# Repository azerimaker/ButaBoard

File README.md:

# ButaBoard
This repo contains all the necessary design, fabrication files and example codes for the ButaBoard development board. ButaBoard is highly inspired by the [Adafruit Circuit Playground Classic](https://www.adafruit.com/product/3000) with some minor hardware changes. Additionaly, the paisley patterned styling and ornamental touches make this board more suitable for wearables. 

## Specs:
- ATmega32u4 MCU, running @3.3V, 8MHz
- 32KB Flash, 2.5 KB SRAM, 1KB EEPROM
- IO pins: 14 (Crocodile clip-4mm Banana pads)
- On-board peripherals:
  - LIS3DH Accelerometer 
  - ALS-PT19-315C analog light sensor
  - AOS3729A analog microphone
  - NTC Temperature Sensor
  - Buzzer
  - 12x WS2812B RGB LEDs
  - 1x user button, 1x user LED
  - Power Switch
- Dimenions: ~94x61x5 mm

### ButaBoard v1

<div align="center">
<br />This work is licensed under a <a rel="license" href="http://creativecommons.org/licenses/by-nc-sa/4.0/">Creative Commons Attribution-NonCommercial-ShareAlike 4.0 International License</a>.
</div>

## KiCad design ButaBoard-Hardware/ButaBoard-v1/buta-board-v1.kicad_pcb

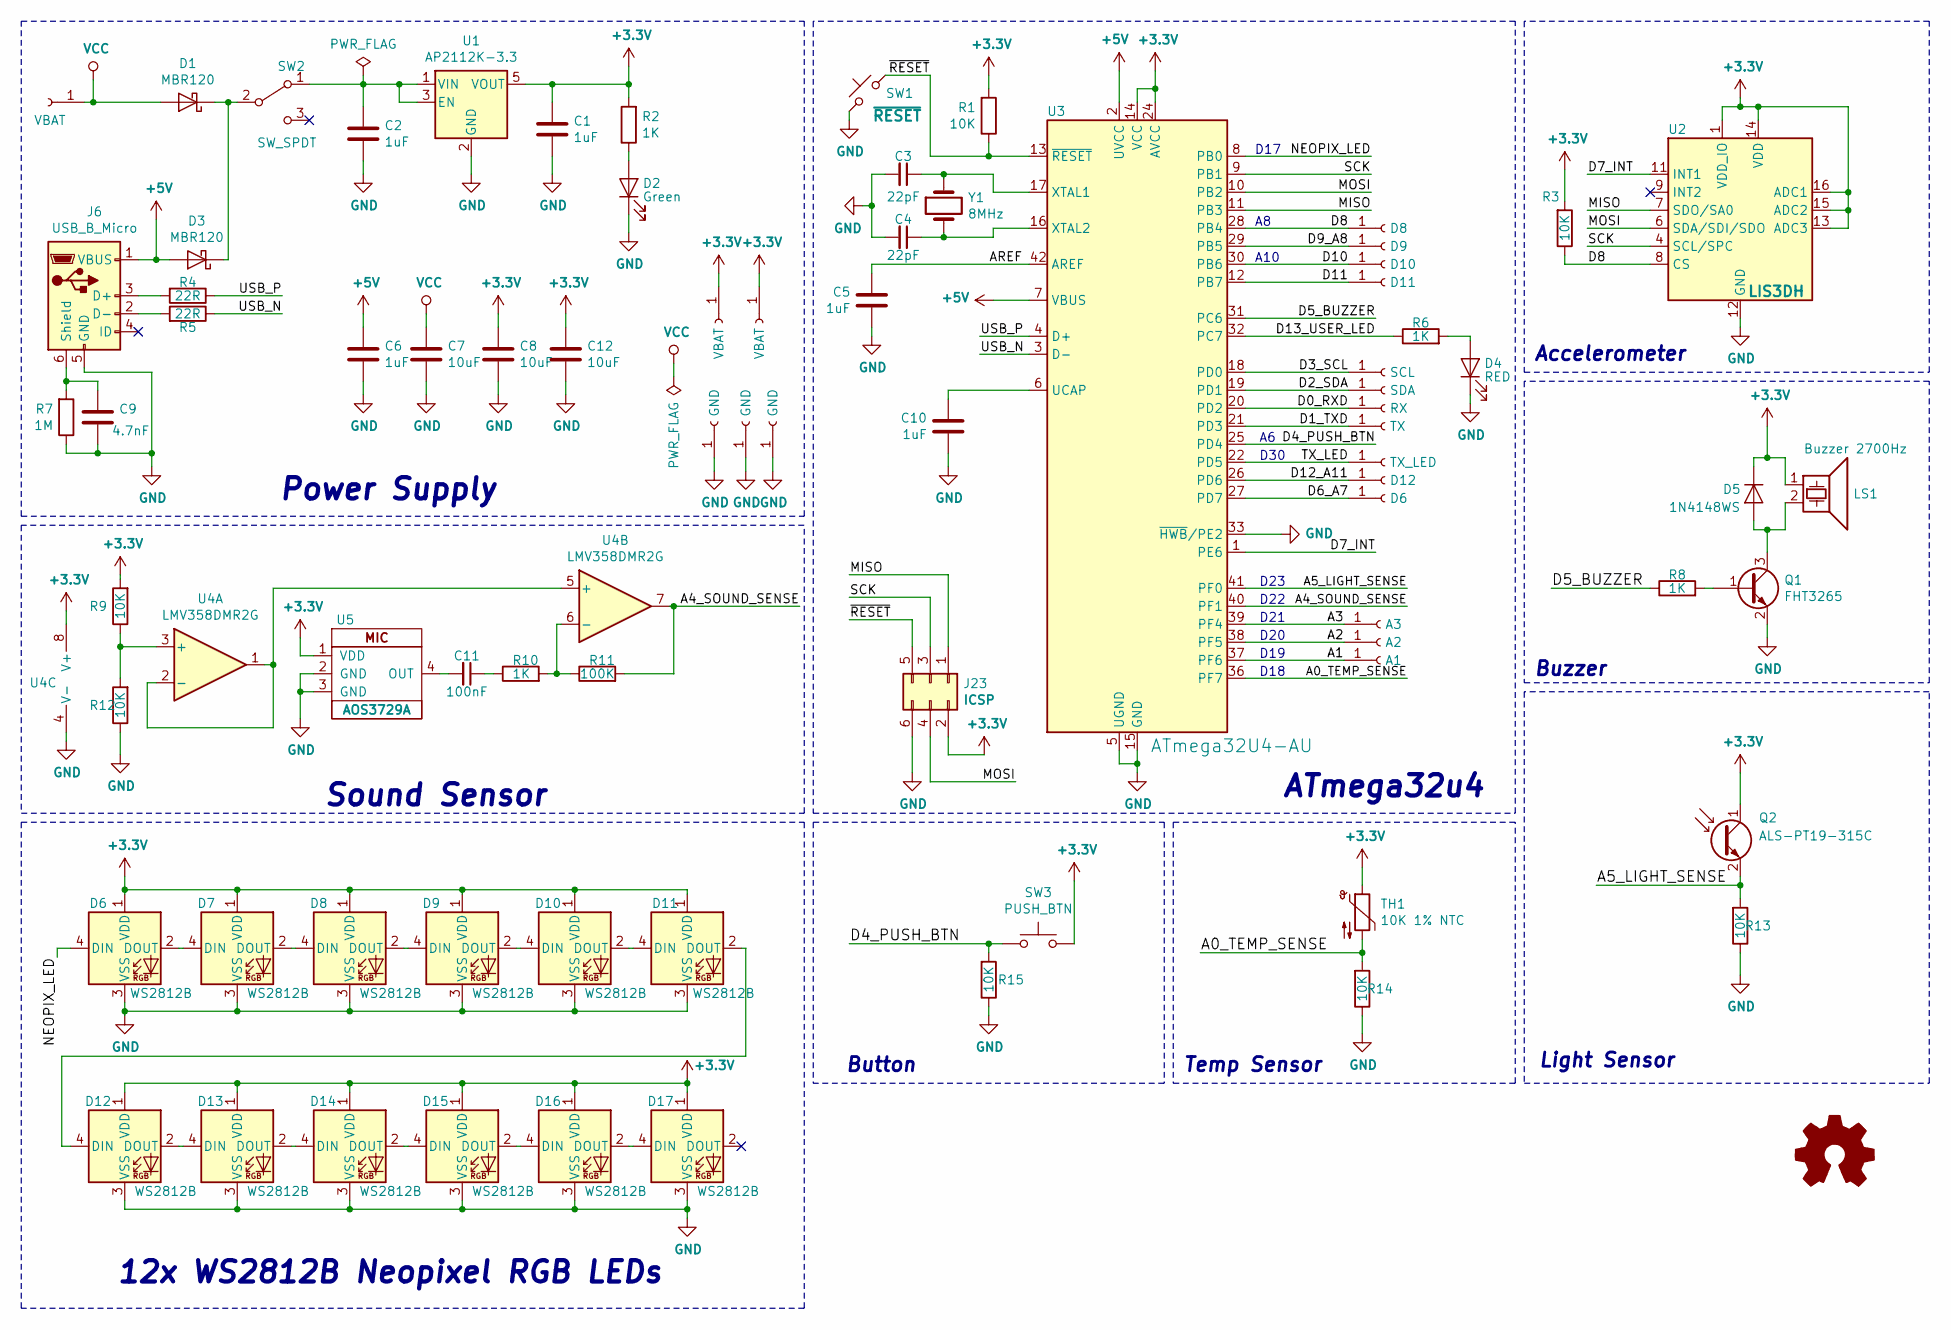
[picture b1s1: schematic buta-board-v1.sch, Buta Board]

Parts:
C1, C2, C5, C6, C10: 1uF; C_0805_2012Metric
C3, C4: 22pF; C_0402_1005Metric
C7, C8, C12: 10uF; C_0805_2012Metric
C9: 4.7nF; C_0805_2012Metric
C11: 100nF; C_0805_2012Metric
D1, D3: MBR120; D_SOD-123; MPN MBR120VLSFT1G
D2: Green; LED_0805_2012Metric
D4: RED; LED_0805_2012Metric
D5: 1N4148WS; D_SOD-323; MPN 1N4148WS
D6, D7, D8, D9, D10, D11, D12, D13, D14, D15, D16, D17: WS2812B; LED_WS2812B_PLCC4_5.0x5.0mm_P3.2mm; MPN WS2812B-B
J2: D8; Alligator_Pads
J3: D9; Alligator_Pads
J4: D10; Alligator_Pads
J5: D11; Alligator_Pads
J6: USB_B_Micro; USB_Micro-B_C10418; MPN C10418
J7, J8, J9: GND; Alligator_Pads
J10: SCL; Alligator_Pads
J11: SDA; Alligator_Pads
J12, J14, J15: VBAT; Alligator_Pads
J13: RX; Alligator_Pads
J16: TX; Alligator_Pads
J17: TX_LED; Alligator_Pads
J18: D12; Alligator_Pads
J19: D6; Alligator_Pads
J20: A3; Alligator_Pads
J21: A2; Alligator_Pads
J22: A1; Alligator_Pads
J23: ICSP; PinHeader_2x03_P2.54mm_Vertical_SMD
LS1: Buzzer 2700Hz; GSC8525RA-16R2700; MPN GSC8525RA-16R2700
Q1: FHT3265; SOT-23; MPN FHT3265-ME
Q2: ALS-PT19-315C; D_0603_1608Metric; MPN ALS-PT19-315C/L177/TR8
R1, R3, R9, R12, R13, R14, R15: 10K; R_0603_1608Metric
R2, R6, R8, R10: 1K; R_0603_1608Metric
R4, R5: 22R; R_0603_1608Metric
R7: 1M; R_0603_1608Metric
R11: 100K; R_0603_1608Metric
SW1: ~RESET; SW_SPST_B3U-1000P-B; MPN B3U-1000P-B
SW2: SW_SPDT; MSS22D18; MPN K3-2235S-F1
SW3: PUSH_BTN; SKHMQKE010_PushButton; MPN SKHMQKE010
TH1: 10K 1% NTC; R_0603_1608Metric_Pad1.05x0.95mm_HandSolder; MPN SDNT1608X103F3380FTF
U1: AP2112K-3.3; SOT-23-5; MPN AP2112K-3.3TRG1
U2: LIS3DH; LGA-16_3x3mm_P0.5mm_LayoutBorder3x5y
U3: ATmega32U4-AU; TQFP-44_10x10mm_P0.8mm
U4: LMV358DMR2G; MSOP-8_3x3mm_P0.65mm; MPN LMV358DMR2G
U5: AOS3729A; AOS3729A-T42-NXC-MIC
Y1: 8MHz; Crystal_SMD_5032-2Pin_5.0x3.2mm; MPN X50328MSB2GI

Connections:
+3V3: C1.1, C8.1, C12.1, D5.1 (K), D6.1 (VDD), D7.1 (VDD), D8.1 (VDD), D9.1 (VDD), D10.1 (VDD), D11.1 (VDD), D12.1 (VDD), D13.1 (VDD), D14.1 (VDD), D15.1 (VDD), D16.1 (VDD), D17.1 (VDD), J14.1, J15.1, J23.2, LS1.1, Q2.1 (C), R1.2, R2.2, R3.2, R9.2, SW3.2, TH1.1, U1.5 (VOUT), U2.1 (VDD_IO), U2.13 (ADC3), U2.14 (VDD), U2.15 (ADC2), U2.16 (ADC1), U3.14 (VCC), U3.24 (AVCC), U3.34 (VCC), U3.44 (AVCC), U4.8 (V+), U5.1 (VDD)
+5V: C6.1, D3.2 (A), J6.1 (VBUS), U3.2 (UVCC), U3.7 (VBUS)
/A0_TEMP_SENSE: R14.2, TH1.2, U3.36 (PF7)
/A1: J22.1, U3.37 (PF6)
/A2: J21.1, U3.38 (PF5)
/A3: J20.1, U3.39 (PF4)
/A4_SOUND_SENSE: R11.2, U3.40 (PF1), U4.7
/A5_LIGHT_SENSE: Q2.2 (E), R13.2, U3.41 (PF0)
/AREF: C5.1, U3.42 (AREF)
/D0_RXD: J13.1, U3.20 (PD2)
/D1_TXD: J16.1, U3.21 (PD3)
/D2_SDA: J11.1, U3.19 (PD1)
/D3_SCL: J10.1, U3.18 (PD0)
/D4_PUSH_BTN: R15.2, SW3.1, U3.25 (PD4)
/D5_BUZZER: R8.1, U3.31 (PC6)
/D6_A7: J19.1, U3.27 (PD7)
/D7_INT: U2.11 (INT1), U3.1 (PE6)
/D8: J2.1, R3.1, U2.8 (CS), U3.28 (PB4)
/D9_A8: J3.1, U3.29 (PB5)
/D10: J4.1, U3.30 (PB6)
/D11: J5.1, U3.12 (PB7)
/D12_A10: J18.1, U3.26 (PD6)
/D13_USER_LED: R6.1, U3.32 (PC7)
/MISO: J23.1, U2.7 (SDO/SA0), U3.11 (PB3)
/MOSI: J23.4, U2.6 (SDA/SDI/SDO), U3.10 (PB2)
/NEOPIX_LED: D6.4 (DIN), U3.8 (PB0)
/SCK: J23.3, U2.4 (SCL/SPC), U3.9 (PB1)
/TX_LED: J17.1, U3.22 (PD5)
/USB_N: R5.1, U3.3 (D-)
/USB_P: R4.1, U3.4 (D+)
/~RESET: J23.5, R1.1, SW1.2, U3.13 (~RESET)
GND: C1.2, C2.2, C3.2, C4.2, C5.2, C6.2, C7.2, C8.2, C9.2, C10.2, C12.2, D2.1 (K), D4.1 (K), D6.3 (VSS), D7.3 (VSS), D8.3 (VSS), D9.3 (VSS), D10.3 (VSS), D11.3 (VSS), D12.3 (VSS), D13.3 (VSS), D14.3 (VSS), D15.3 (VSS), D16.3 (VSS), D17.3 (VSS), J6.5 (GND), J7.1, J8.1, J9.1, J23.6, Q1.2 (E), R7.1, R12.1, R13.1, R14.1, R15.1, SW1.1, U1.2 (GND), U2.5 (GND), U2.10 (GND), U2.12 (GND), U3.5 (UGND), U3.15 (GND), U3.23 (GND), U3.33 (~HWB~/PE2), U3.35 (GND), U3.43 (GND), U4.4 (V-), U5.2 (GND), U5.3 (GND)
unnamed: C2.1, SW2.1 (A), U1.1 (VIN), U1.3 (EN)
unnamed: C3.1, U3.17 (XTAL1), Y1.1
unnamed: C4.1, U3.16 (XTAL2), Y1.2
unnamed: C9.1, J6.6 (Shield), R7.2
unnamed: C10.1, U3.6 (UCAP)
unnamed: C11.1, R10.1
unnamed: C11.2, U5.4 (OUT)
unnamed: D1.1 (K), D3.1 (K), SW2.2 (B)
unnamed: D2.2 (A), R2.1
unnamed: D4.2 (A), R6.2
unnamed: D5.2 (A), LS1.2, Q1.3 (C)
unnamed: D6.2 (DOUT), D7.4 (DIN)
unnamed: D7.2 (DOUT), D8.4 (DIN)
unnamed: D8.2 (DOUT), D9.4 (DIN)
unnamed: D10.2 (DOUT), D11.4 (DIN)
unnamed: D9.2 (DOUT), D10.4 (DIN)
unnamed: D11.2 (DOUT), D12.4 (DIN)
unnamed: D12.2 (DOUT), D13.4 (DIN)
unnamed: D13.2 (DOUT), D14.4 (DIN)
unnamed: D14.2 (DOUT), D15.4 (DIN)
unnamed: D15.2 (DOUT), D16.4 (DIN)
unnamed: D16.2 (DOUT), D17.4 (DIN)
unnamed: J6.2 (D-), R5.2
unnamed: J6.3 (D+), R4.2
unnamed: Q1.1 (B), R8.2
unnamed: R10.2, R11.1, U4.6 (-)
unnamed: R9.1, R12.2, U4.3 (+)
unnamed: U4.1, U4.2 (-), U4.5 (+)
VCC: C7.1, D1.2 (A), J12.1

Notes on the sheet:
Power Supply
12x WS2812B Neopixel RGB LEDs
ATmega32u4
Sound Sensor
Accelerometer
Buzzer
Light Sensor
Temp Sensor
Button
D17
A10
D30
D23
D22
D18
D20
D21
D19

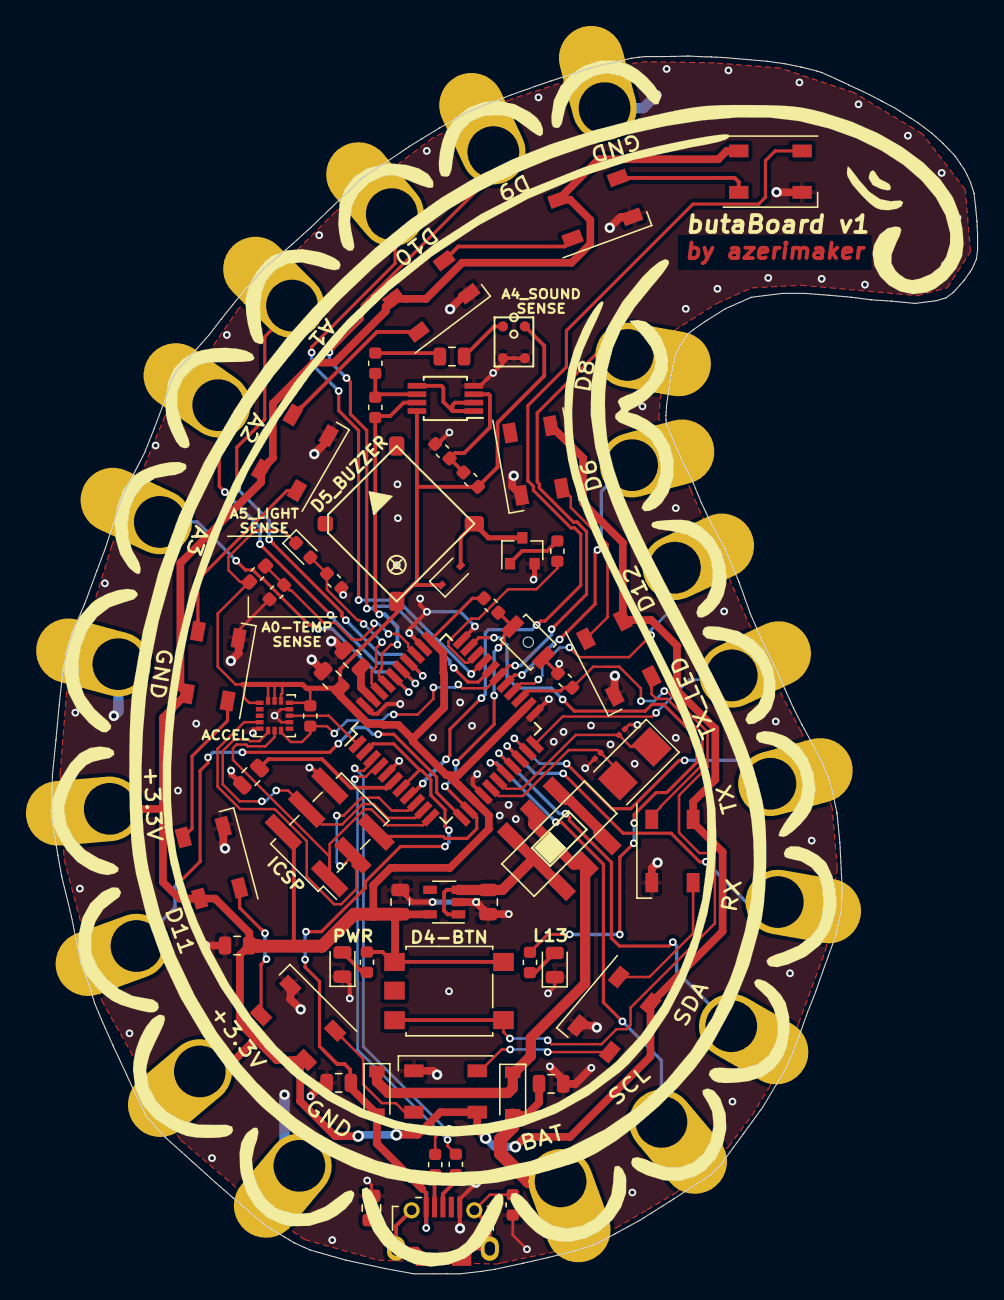
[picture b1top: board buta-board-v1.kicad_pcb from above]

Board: 2 copper layers, 71.6 x 94.2 mm, 79 parts (0 on the bottom side), 61 nets.

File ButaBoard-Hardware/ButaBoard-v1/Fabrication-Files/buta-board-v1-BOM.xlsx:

Reference | Quantity | MPN | Value | Description | Package | URL
C11 | 1 |  | 100nF |  | 0805_2012Metric | ~
C2 C6 C1 C5 C10 | 5 |  | 1uF |  | 0805_2012Metric | ~
C3 C4 | 2 |  | 22pF |  | 0201_0603Metric | ~
C8 C7 C12 | 3 |  | 10uF |  | 0805_2012Metric | ~
C9 | 1 |  | 4.7nF |  | 0805_2012Metric | ~
D1 D3 | 2 | MBR120VLSFT1G | MBR120 | Schottky Barrier Diodes (SBD) SOD-123F RoHS | SMD:D_SOD-123 | https://lcsc.com/product-detail/Schottky-Barrier-Diodes-SBD_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
D2 | 1 |  | Green |  | 0805_2012Metric | ~
D4 | 1 |  | RED |  | 0805_2012Metric | ~
D5 | 1 | 1N4148WS | 1N4148WS | Switching Diode 75V 150mA 1V @ 10mA 4ns SOD-323 RoHS | SOD-323 | https://lcsc.com/product-detail/Switching-Diode_1N4148WS_C11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
D6 D7 D8 D9 D10 D11 D12 D13 D14 D15 D17 D16 | 12 | WS2812B-B | WS2812B | Light Emitting Diodes (LED) RGB 620~630nm Red, 515~530nm Green, 465~475nm Blue 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 | LED_WS2812B_PLCC4_5.0x5.0mm_P3.2mm
J23 | 1 |  | ICSP |  | PinHeader_2x03_P2.54mm_Vertical_SMD | https://lcsc.com/product-detail/Light-Emitting-Diodes-LED_50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
J6 | 1 | C10418 | USB_B_Micro | USB Connectors 5 Receptacle 1 SMD RoHS | USB_Micro-B_C10418 | https://lcsc.com/product-detail/USB-Connectors_Jing-Extensio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
LS1 | 1 | GSC8525RA-16R2700 | Buzzer 2700Hz | Buzzers Magnetic NO 2700Hz 3V 2 ~ 5V 8.5mm x 8.5mm SMD,8.5x8.5x3mm RoHS | SMD,8.5x8.5x3mm | https://lcsc.com/product-detail/Buzzers_INGHAi-GSC8525RA-16R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
Q1 | 1 | FHT3265-ME | FHT3265 | Transistors (NPN/PNP) NPN 800mA 30V SOT-23(SOT-23-3) RoHS | SOT-23 | https://lcsc.com/product-detail/Others_Guangdong-Fenghua-Adv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
Q2 | 1 | ALS-PT19-315C/L177/TR8 | ALS-PT19-315C | Ambient Light Sensors 1.7*0.8*0.6mm RoHS | D_0603_1608Metric – 1.7*0.8*0.6mm | https://lcsc.com/product-detail/Photoresistors_ALS-PT19-315C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
R1 R3 R13 R14 R15 R9 R12 | 7 |  | 10K |  | 0603_1608Metric | ~
R11 | 1 |  | 100K |  | 0603_1608Metric | ~
R2 R6 R8 R10 | 4 |  | 1K |  | 0603_1608Metric | ~
R4 R5 | 2 |  | 22R |  | 0603_1608Metric | ~
R7 | 1 |  | 1M |  | 0603_1608Metric | ~
SW1 | 1 | B3U-1000P-B | ~RESET |  | SW_SPST_B3U-1000P-B | ~
SW2 | 1 | K3-2235S-F1 | SW_SPDT | 9.0mm*3.5mm SMD | MSS22D18 | https://lcsc.com/product-detail/Toggle-Switches_Korean-Hropa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
SW3 | 1 | SKHMQKE010 | PUSH_BTN | Tactile Switches SPST-NO 6.50mm x 6.20mm 3.10mm 50mA @ 12VDC SMD RoHS | SKHMQKE010_PushButton | https://lcsc.com/product-detail/Tactile-Switches_ALPS_SKHMQK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
TH1 | 1 | SDNT1608X103F3380FTF | 10K 1% NTC | NTC Thermistors 1/10W 10KOhms ±1% 3380K 0603 RoHS | 0603_1608Metric_Pad1.05x0.95mm_HandSolder | https://lcsc.com/product-detail/Others_Sunlord-SDNT1608X103F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
U1 | 1 | AP2112K-3.3TRG1 | AP2112K-3.3 | Low Dropout Regulators(LDO) SOT-25 RoHS | SOT-23-5 | https://lcsc.com/product-detail/Low-Dropout-Regulators-LDO_D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
U2 | 1 | LIS3DH | LIS3DH |  | LGA-16_3x3mm_P0.5mm_LayoutBorder3x5y | Aliexpress
U3 | 1 | ATmega32U4-AU | ATmega32U4-AU | ATMEL & AVR QFP-44_10x10x08P RoHS | TQFP-44_10x10mm_P0.8mm | https://lcsc.com/product-detail/ATMEL-AVR_ATMEL_ATMEGA32U4-A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
U4 | 1 | LMV358DMR2G | LMV358DMR2G | General Purpose Amplifiers General Purpose 2 2.7V ~ 5.5V 1MHz 1 V/us MSOP-8 RoHS | MSOP-8_3x3mm_P0.65mm | https://lcsc.com/product-detail/General-Purpose-Amplifiers_O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
U5 | 1 | AOS3729A | AOS3729A | Electret Condenser Microphone SMD,3.76x2.95x1.10mm RoHS | AOS3729A-T42-NXC-MIC | https://lcsc.com/product-detail/Others_SANICO-AOS3729A-T42-N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
Y1 | 1 | X50328MSB2GI | 8MHz | Tactile Switches SPST-NO 6.50mm x 6.20mm 3.10mm 50mA @ 12VDC SMD RoHS | Crystal_SMD_5032-2Pin_5.0x3.2mm | https://lcsc.com/product-detail/SMD-Crystal-Resonators_Yangx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

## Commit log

2019-09-10 Design files added
    Design files for v1
2019-09-10 Folder Structure Update
